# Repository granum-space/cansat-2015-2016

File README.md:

# main
Код для полётного модуля

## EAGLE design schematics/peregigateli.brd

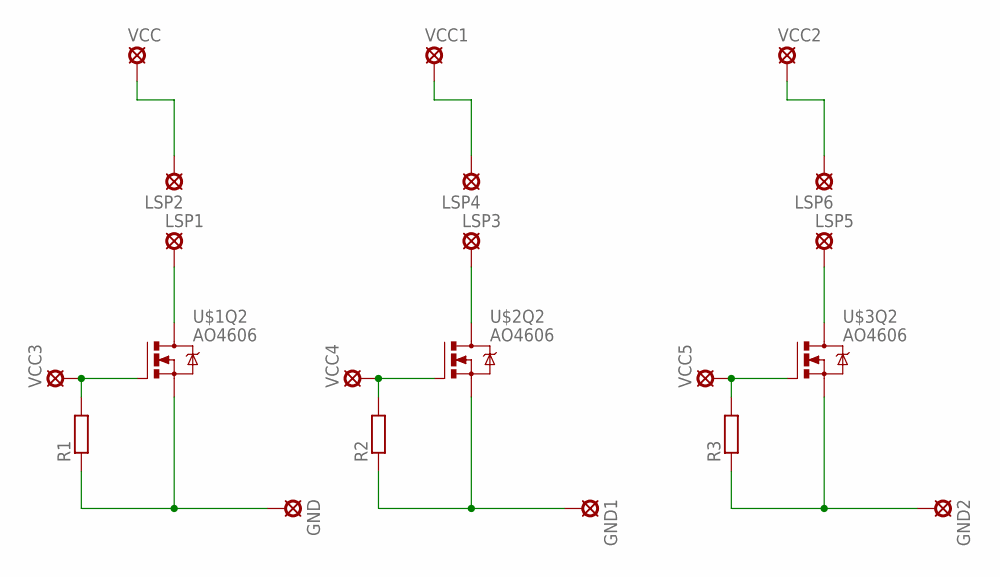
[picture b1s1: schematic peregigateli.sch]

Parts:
GND, GND1, GND2: LSP10
LSP1, LSP2, LSP3, LSP4, LSP5, LSP6: LSP10
R1, R2, R3: R-EU_0207/10; 0207/10
U$1, U$2, U$3: AO4606; SOIC-8
VCC, VCC1, VCC2, VCC3, VCC4, VCC5: LSP10

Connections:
unnamed: LSP1.MP, U$1.7 (D), U$1.8 (D)
unnamed: R1.2, U$1.2 (G), VCC3.MP
unnamed: GND.MP, R1.1, U$1.1 (S)
unnamed: LSP3.MP, U$2.7 (D), U$2.8 (D)
unnamed: LSP4.MP, VCC1.MP
unnamed: GND1.MP, R2.1, U$2.1 (S)
unnamed: LSP5.MP, U$3.7 (D), U$3.8 (D)
unnamed: LSP6.MP, VCC2.MP
unnamed: GND2.MP, R3.1, U$3.1 (S)
unnamed: LSP2.MP, VCC.MP
unnamed: R2.2, U$2.2 (G), VCC4.MP
unnamed: R3.2, U$3.2 (G), VCC5.MP

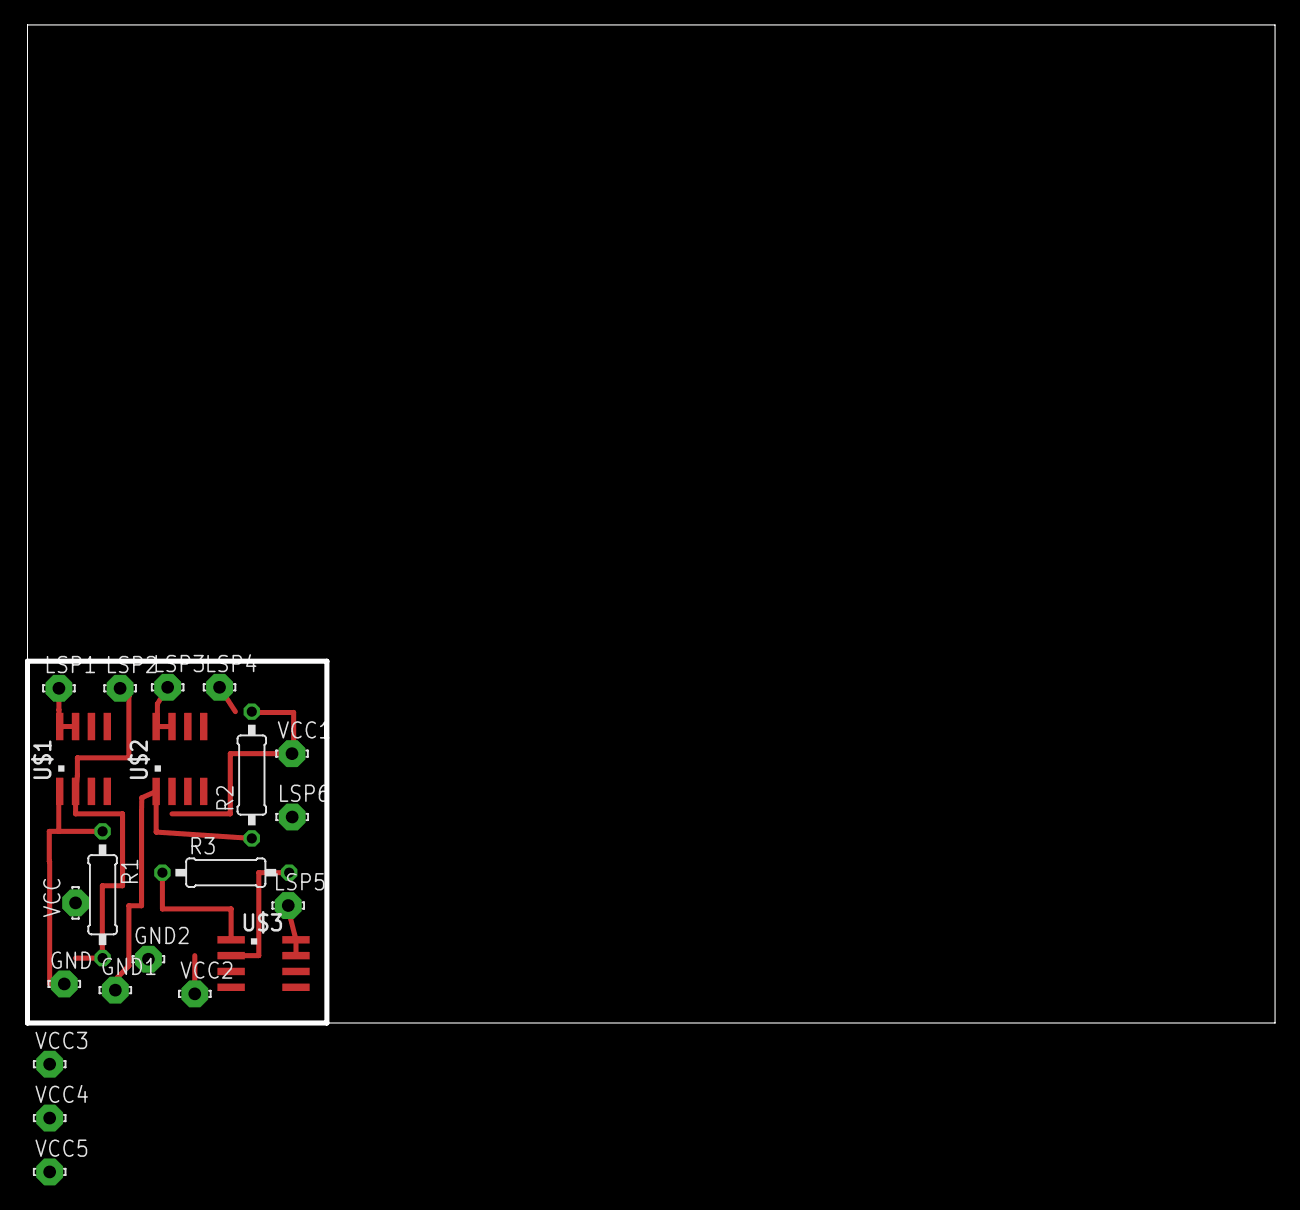
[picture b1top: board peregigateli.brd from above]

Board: 2 copper layers, 100.0 x 80.0 mm, 21 parts (0 on the bottom side), 12 nets.

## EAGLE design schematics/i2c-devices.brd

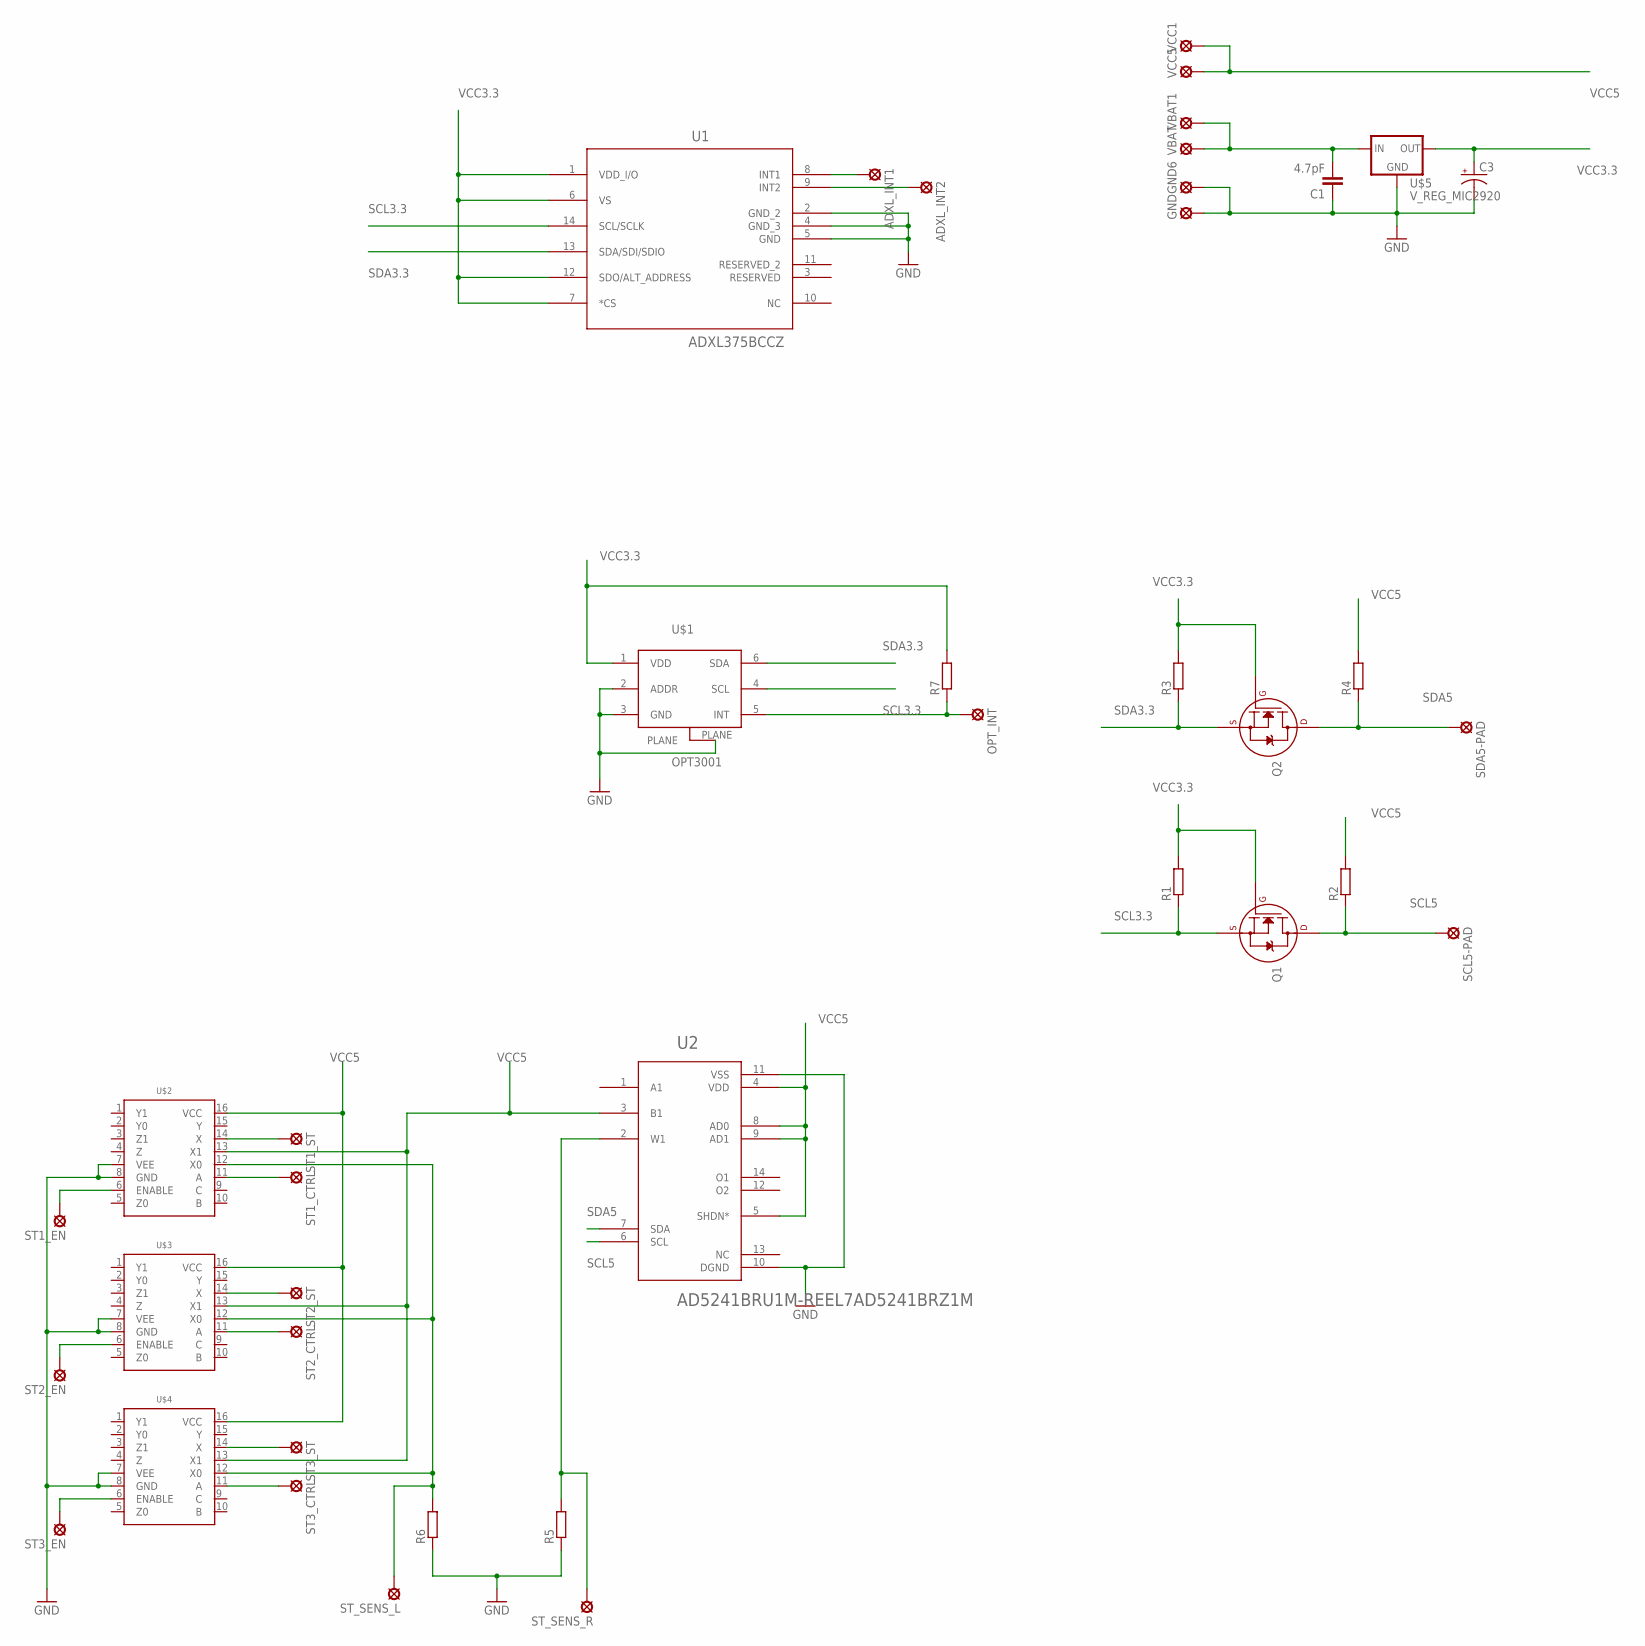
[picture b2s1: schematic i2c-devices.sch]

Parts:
ADXL_INT1, ADXL_INT2: LSP10
C1: 4.7pF; C0603
C3: CAP_POL3528; EIA3528
GND, GND6: LSP10
OPT_INT: LSP10
Q1, Q2: 2N7002_SOT23; SOT-23
R1, R2, R3, R4, R5, R6, R7: R-EU_R0805; R0805
SCL5-PAD: LSP10
SDA5-PAD: LSP10
ST1_CTRL, ST1_EN, ST1_ST, ST2_CTRL, ST2_EN, ST2_ST, ST3_CTRL, ST3_EN, ST3_ST: LSP10
ST_SENS_L: LSP10
ST_SENS_R: LSP10
U1: ADXL375BCCZ; LGA_CC-14-1
U2: AD5241BRU1M-REEL7AD5241BRZ1M; SOIC-14
U$1: OPT3001
U$2, U$3, U$4: MC74HC4051AMC74HC4051AG; SOIC-16
U$5: V_REG_MIC2920; SOT223
VBAT, VBAT1: LSP10
VCC1, VCC5: LSP10

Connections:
GND: C1.1, C3.C (-), GND.MP, GND6.MP, R5.1, R6.1, U1.2 (GND_2), U1.4 (GND_3), U1.5 (GND), U2.10 (DGND), U2.11 (VSS), U$1.2 (ADDR), U$1.3 (GND), U$1.PLANE, U$2.7 (VEE), U$2.8 (GND), U$3.7 (VEE), U$3.8 (GND), U$4.7 (VEE), U$4.8 (GND), U$5.2 (GND)
unnamed: C1.2, U$5.1 (IN), VBAT.MP, VBAT1.MP
unnamed: ST1_ST.MP, U$2.14 (X)
unnamed: ST1_EN.MP, U$2.6 (ENABLE)
unnamed: ST3_EN.MP, U$4.6 (ENABLE)
unnamed: ST2_ST.MP, U$3.14 (X)
unnamed: ST3_ST.MP, U$4.14 (X)
unnamed: R5.2, ST_SENS_R.MP, U2.2 (W1)
unnamed: R6.2, ST_SENS_L.MP, U$2.12 (X0), U$3.12 (X0), U$4.12 (X0)
unnamed: ST2_EN.MP, U$3.6 (ENABLE)
unnamed: ST2_CTRL.MP, U$3.11 (A)
unnamed: ST3_CTRL.MP, U$4.11 (A)
unnamed: ST1_CTRL.MP, U$2.11 (A)
unnamed: OPT_INT.MP, R7.1, U$1.5 (INT)
unnamed: ADXL_INT1.MP, U1.8 (INT1)
unnamed: ADXL_INT2.MP, U1.9 (INT2)
SCL3.3: Q1.2 (S), R1.1, U1.14 (SCL/SCLK), U$1.4 (SCL)
SCL5: Q1.3 (D), R2.1, SCL5-PAD.MP, U2.6 (SCL)
SDA3.3: Q2.2 (S), R3.1, U1.13 (SDA/SDI/SDIO), U$1.6 (SDA)
SDA5: Q2.3 (D), R4.1, SDA5-PAD.MP, U2.7 (SDA)
VCC3.3: C3.A (+), Q1.1 (G), Q2.1 (G), R1.2, R3.2, R7.2, U1.1 (VDD_I/O), U1.6 (VS), U1.7 (*CS), U1.12 (SDO/ALT_ADDRESS), U$1.1 (VDD), U$5.3 (OUT)
VCC5: R2.2, R4.2, U2.3 (B1), U2.4 (VDD), U2.5 (SHDN*), U2.8 (AD0), U2.9 (AD1), U$2.13 (X1), U$2.16 (VCC), U$3.13 (X1), U$3.16 (VCC), U$4.13 (X1), U$4.16 (VCC), VCC1.MP, VCC5.MP

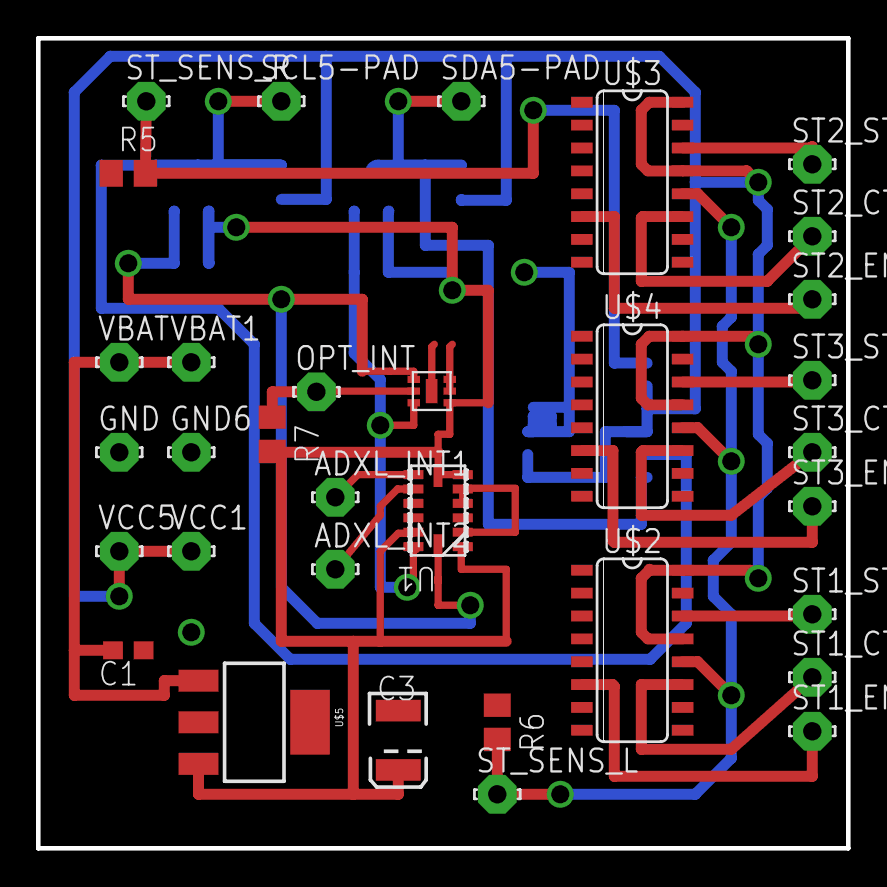
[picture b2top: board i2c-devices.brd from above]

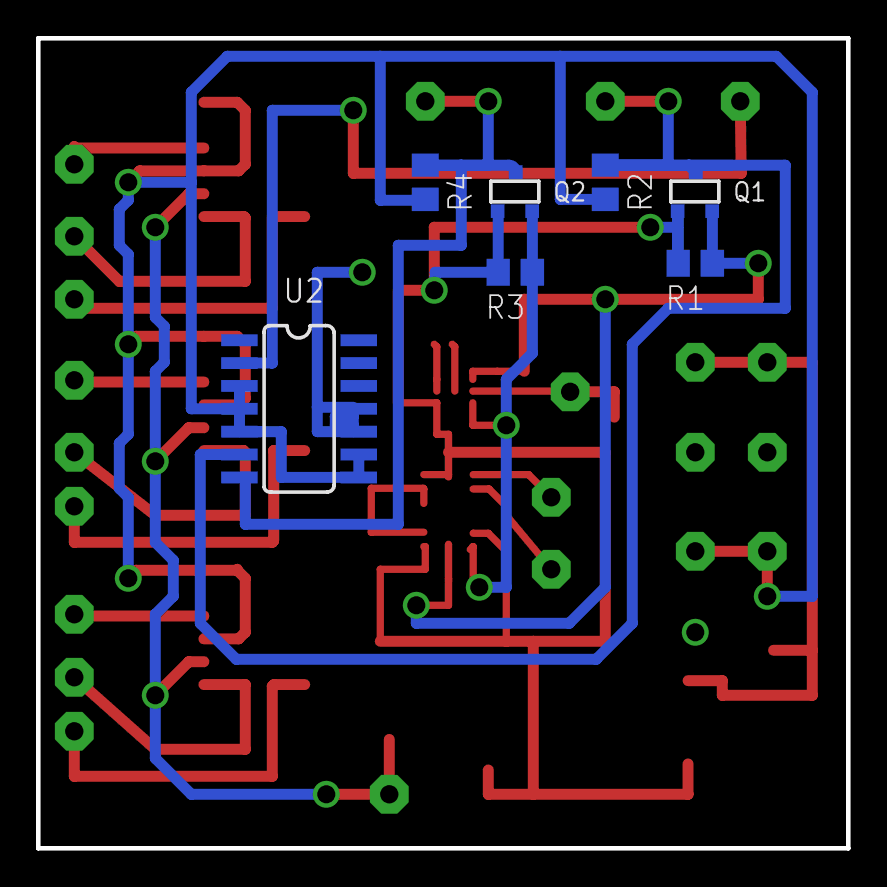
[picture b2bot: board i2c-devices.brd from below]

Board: 2 copper layers, 45.0 x 45.0 mm, 40 parts (7 on the bottom side), 22 nets.

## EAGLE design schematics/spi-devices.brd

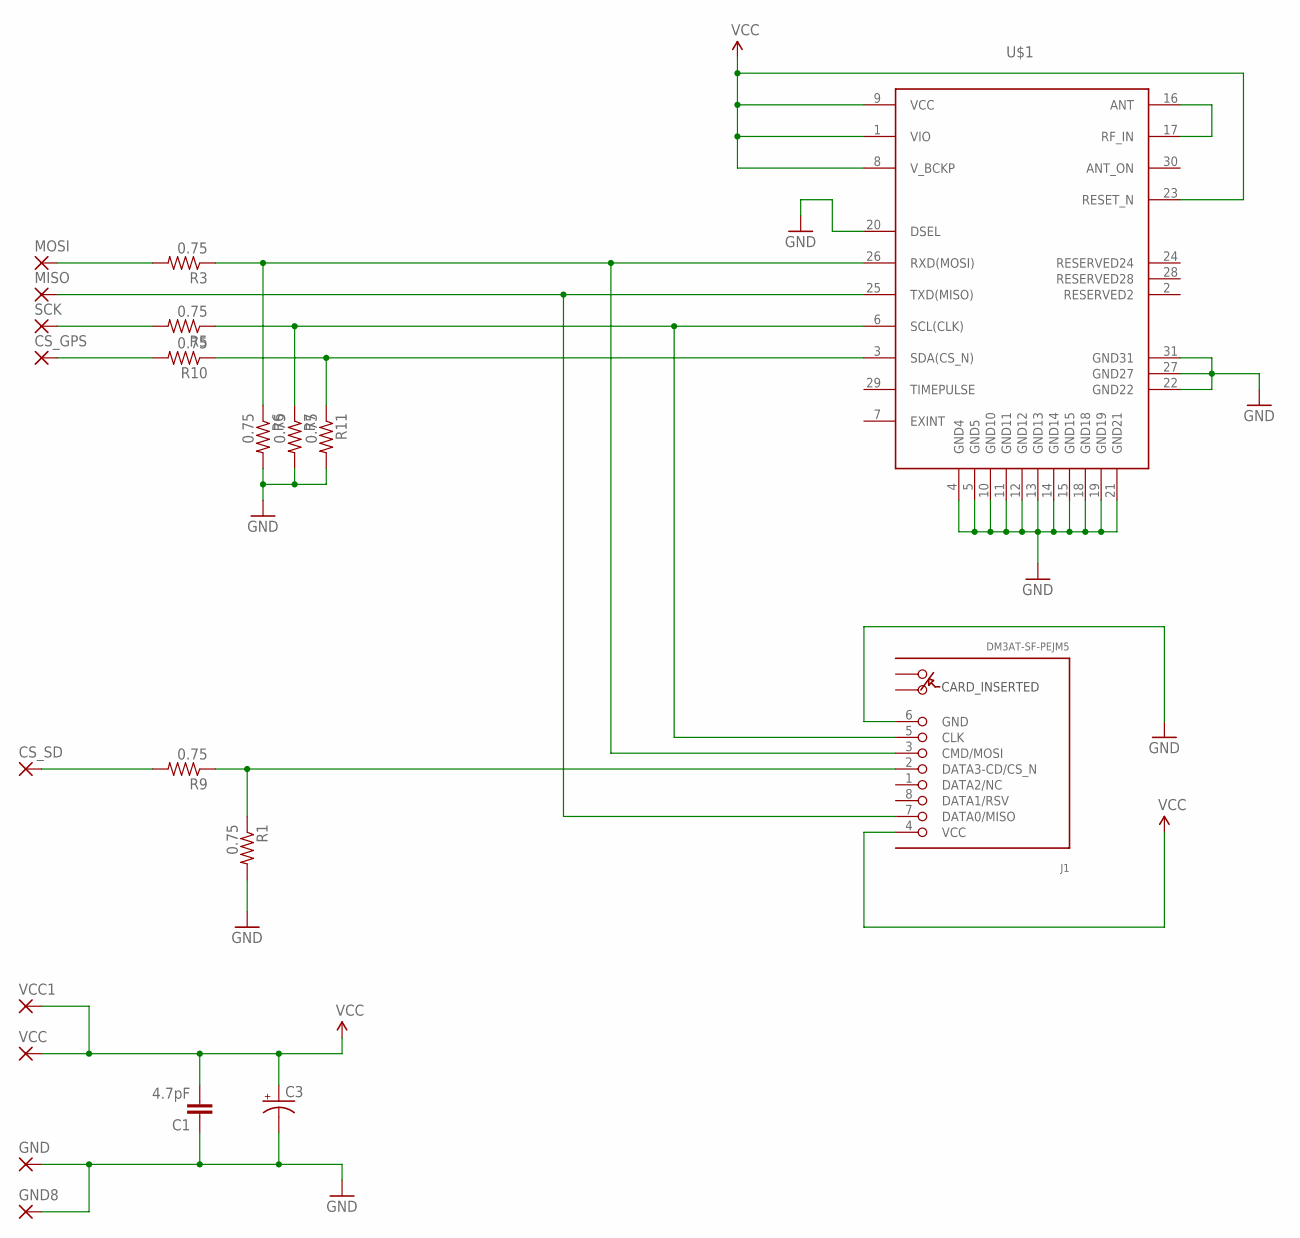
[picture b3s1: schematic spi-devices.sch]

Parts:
C1: 4.7pF; C0603
C3: CAP_POL3528; EIA3528
CS_GPS: 2,54/0,9
CS_SD: 2,54/0,9
GND, GND8: 2,54/0,9
J1: DM3AT-SF-PEJM5
MISO: 2,54/0,9
MOSI: 2,54/0,9
R1, R3, R5, R6, R7, R9, R10, R11: 0.75; 0805
SCK: 2,54/0,9
U$1: CAM-M8Q
VCC, VCC1: 2,54/0,9

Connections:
CS_GPS: CS_GPS.1, R10.2
CS_GPS_3.3: R10.1, R11.1, U$1.3 (SDA(CS_N))
CS_SD: CS_SD.1, R9.2
CS_SD_3.3: J1.2 (DATA3-CD/CS_N), R1.1, R9.1
GND: C1.1, C3.C (-), GND.1, GND8.1, J1.6 (GND), R1.2, R6.2, R7.2, R11.2, U$1.4 (GND4), U$1.5 (GND5), U$1.10 (GND10), U$1.11 (GND11), U$1.12 (GND12), U$1.13 (GND13), U$1.14 (GND14), U$1.15 (GND15), U$1.18 (GND18), U$1.19 (GND19), U$1.20 (DSEL), U$1.21 (GND21), U$1.22 (GND22), U$1.27 (GND27), U$1.31 (GND31)
MISO: J1.7 (DATA0/MISO), MISO.1, U$1.25 (TXD(MISO))
MOSI: MOSI.1, R3.2
MOSI3.3: J1.3 (CMD/MOSI), R3.1, R6.1, U$1.26 (RXD(MOSI))
RF: U$1.16 (ANT), U$1.17 (RF_IN)
SCK: R5.2, SCK.1
SCK3.3: J1.5 (CLK), R5.1, R7.1, U$1.6 (SCL(CLK))
VCC: C1.2, C3.A (+), J1.4 (VCC), U$1.1 (VIO), U$1.8 (V_BCKP), U$1.9 (VCC), U$1.23 (RESET_N), VCC.1, VCC1.1

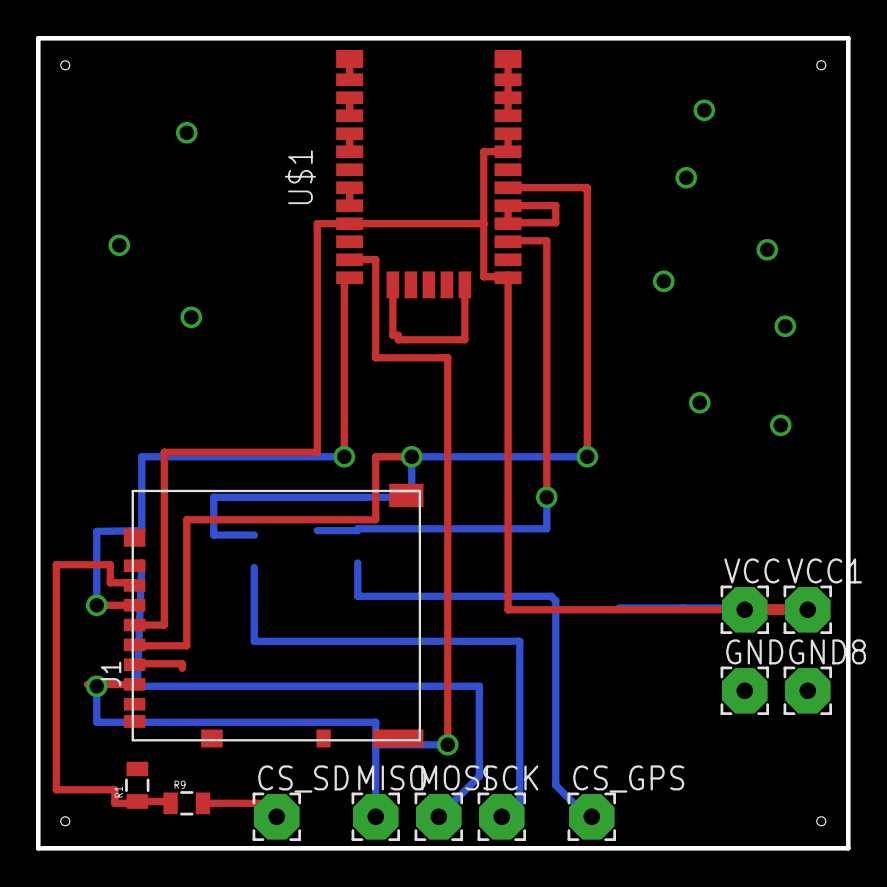
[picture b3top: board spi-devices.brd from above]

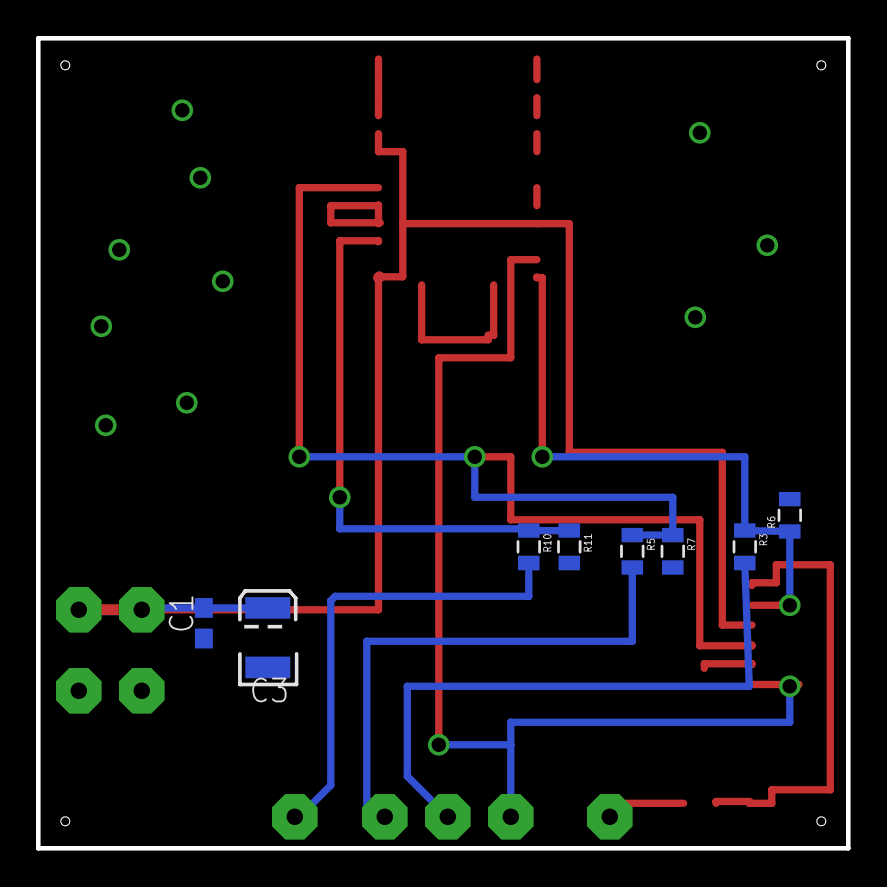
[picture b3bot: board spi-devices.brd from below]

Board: 2 copper layers, 45.0 x 45.0 mm, 21 parts (8 on the bottom side), 12 nets.

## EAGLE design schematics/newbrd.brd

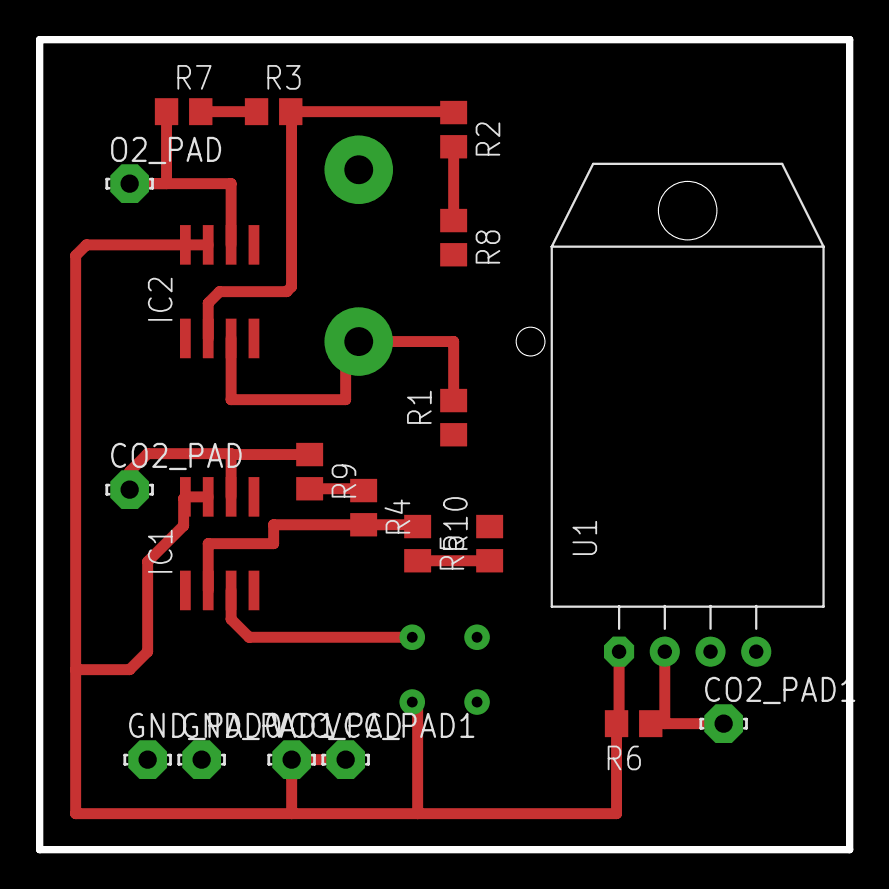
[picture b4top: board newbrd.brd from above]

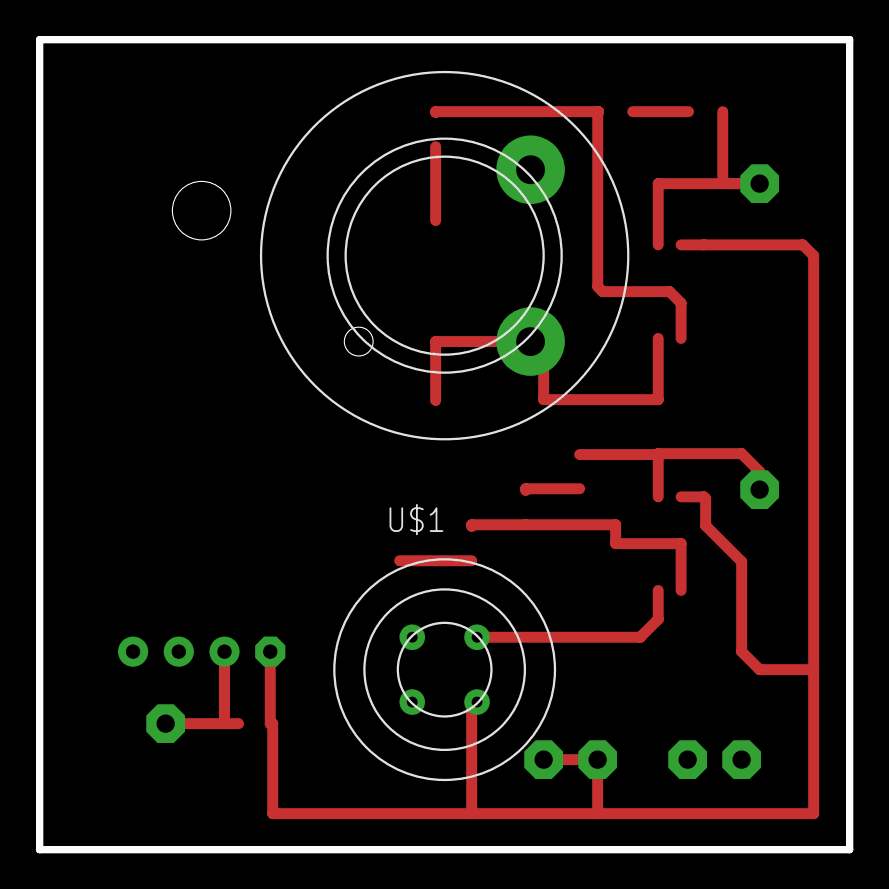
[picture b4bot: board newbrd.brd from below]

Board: 2 copper layers, 45.0 x 45.0 mm, 22 parts (2 on the bottom side), 13 nets.

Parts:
CO2_PAD, CO2_PAD1: LSP10
GND_PAD0, GND_PAD1: LSP10
IC1, IC2: TLC271D; SO08
O2_PAD: LSP10
R1, R2, R3, R4, R5, R6, R7, R8, R9, R10: R0805
U1: RHT03_DHT-22/RA
U$1: TGS4161
U$2: O2-A2
VCC_PAD, VCC_PAD1: LSP10

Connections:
GND: GND_PAD0.MP, GND_PAD1.MP, IC1.4, IC2.4, R1.1, R8.2, R10.2, U1.GND, U$1.3, U$1.4, U$2.GND
unnamed: IC2.3, R1.2, U$2.VOUT
unnamed: CO2_PAD1.MP, R6.1, U1.DATA
unnamed: IC2.2, R2.1, R3.2
unnamed: IC2.6, O2_PAD.MP, R7.1
unnamed: IC1.3, U$1.2
unnamed: CO2_PAD.MP, IC1.6, R9.1
unnamed: R3.1, R7.2
unnamed: R2.2, R8.1
unnamed: R4.1, R9.2
unnamed: R5.2, R10.1
unnamed: IC1.2, R4.2, R5.1
VCC: IC1.7, IC1.8, IC2.7, IC2.8, R6.2, U1.VDD, U$1.1, VCC_PAD.MP, VCC_PAD1.MP

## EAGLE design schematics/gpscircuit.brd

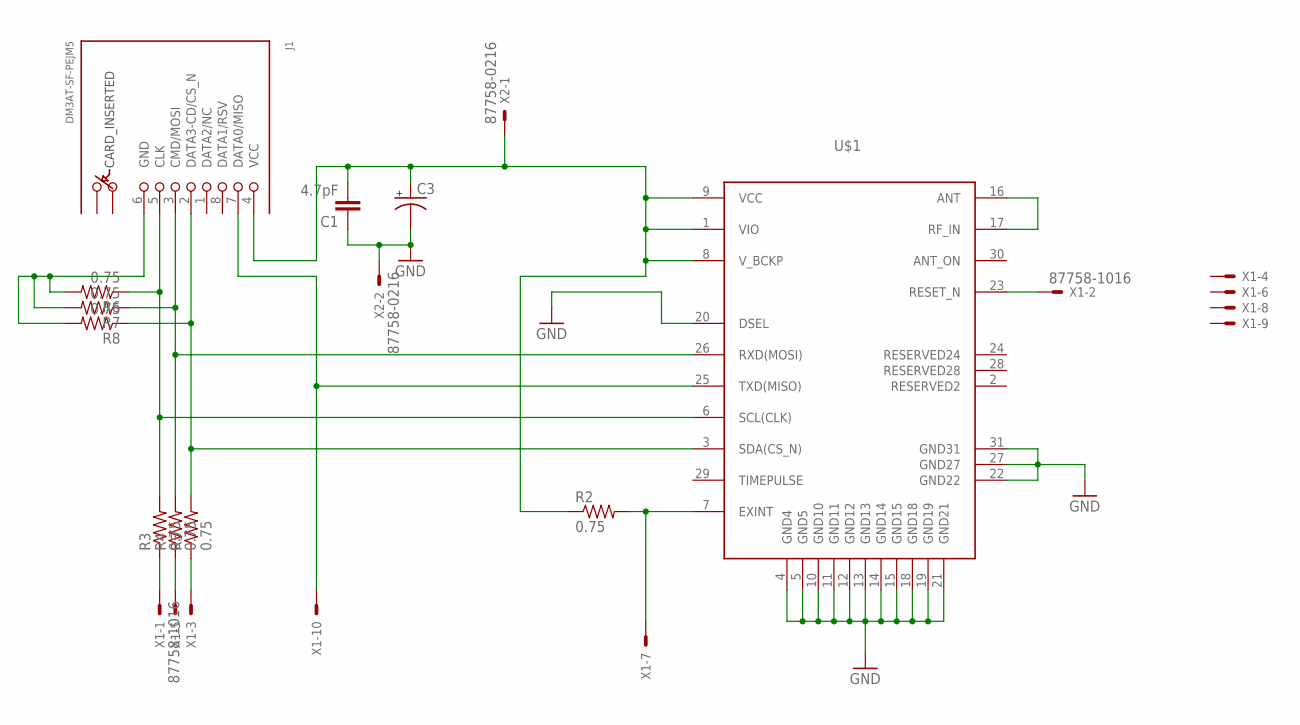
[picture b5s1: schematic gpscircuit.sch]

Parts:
C1: 4.7pF; C0603
C3: CAP_POL3528; EIA3528
J1: DM3AT-SF-PEJM5
R2, R3, R4, R5, R6, R7, R8: 0.75; 0805
U$1: CAM-M8Q
X1: 87758-1016
X2: 87758-0216

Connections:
3.3V: C1.2, C3.A (+), J1.4 (VCC), R2.1, U$1.1 (VIO), U$1.8 (V_BCKP), U$1.9 (VCC), X2.1
GND: C1.1, C3.C (-), U$1.4 (GND4), U$1.5 (GND5), U$1.10 (GND10), U$1.11 (GND11), U$1.12 (GND12), U$1.13 (GND13), U$1.14 (GND14), U$1.15 (GND15), U$1.18 (GND18), U$1.19 (GND19), U$1.20 (DSEL), U$1.21 (GND21), U$1.22 (GND22), U$1.27 (GND27), U$1.31 (GND31), X2.2
unnamed: U$1.16 (ANT), U$1.17 (RF_IN)
unnamed: U$1.23 (RESET_N), X1.2
unnamed: R2.2, U$1.7 (EXINT), X1.7
unnamed: J1.7 (DATA0/MISO), U$1.25 (TXD(MISO)), X1.10
unnamed: R4.1, X1.5
unnamed: R5.1, X1.3
unnamed: J1.6 (GND), R6.2, R7.2, R8.2
unnamed: R3.1, X1.1
unnamed: J1.5 (CLK), R3.2, R6.1, U$1.6 (SCL(CLK))
unnamed: J1.2 (DATA3-CD/CS_N), R5.2, R8.1, U$1.3 (SDA(CS_N))
unnamed: J1.3 (CMD/MOSI), R4.2, R7.1, U$1.26 (RXD(MOSI))

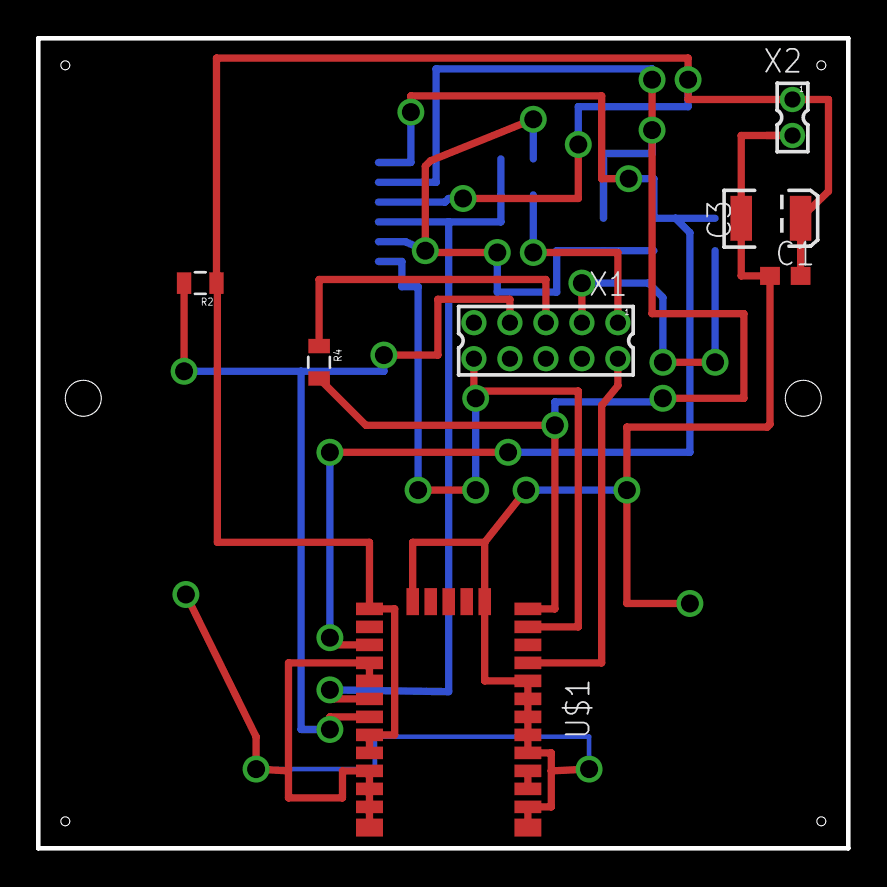
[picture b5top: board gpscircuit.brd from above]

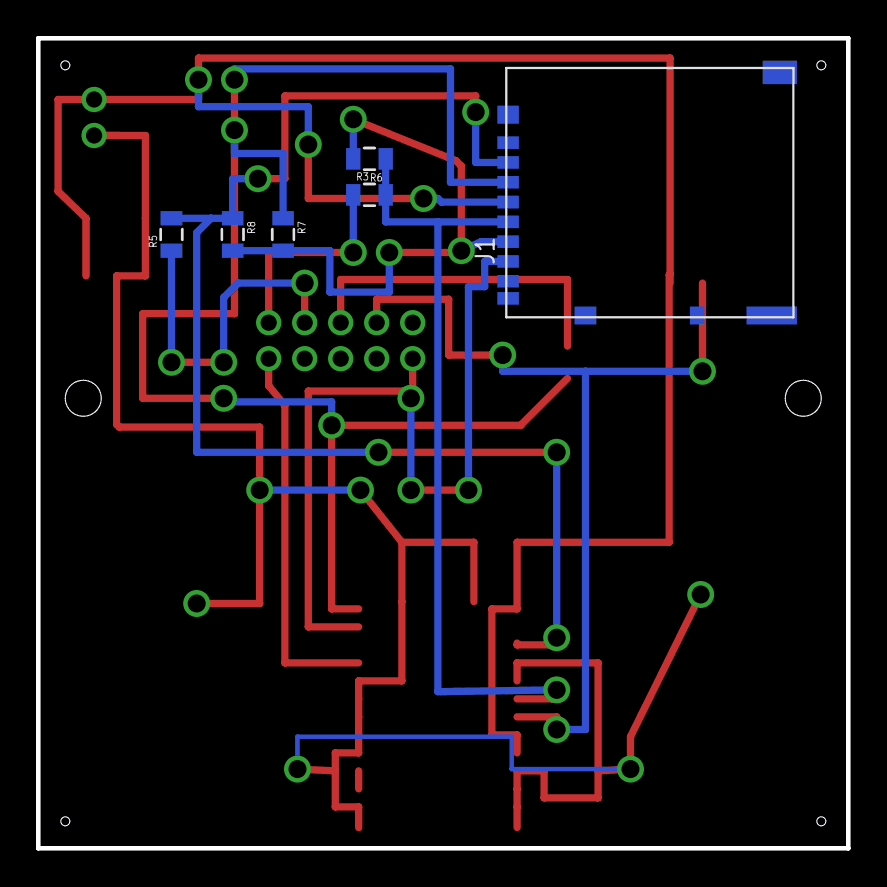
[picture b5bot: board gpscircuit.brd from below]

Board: 2 copper layers, 45.0 x 45.0 mm, 13 parts (6 on the bottom side), 13 nets.

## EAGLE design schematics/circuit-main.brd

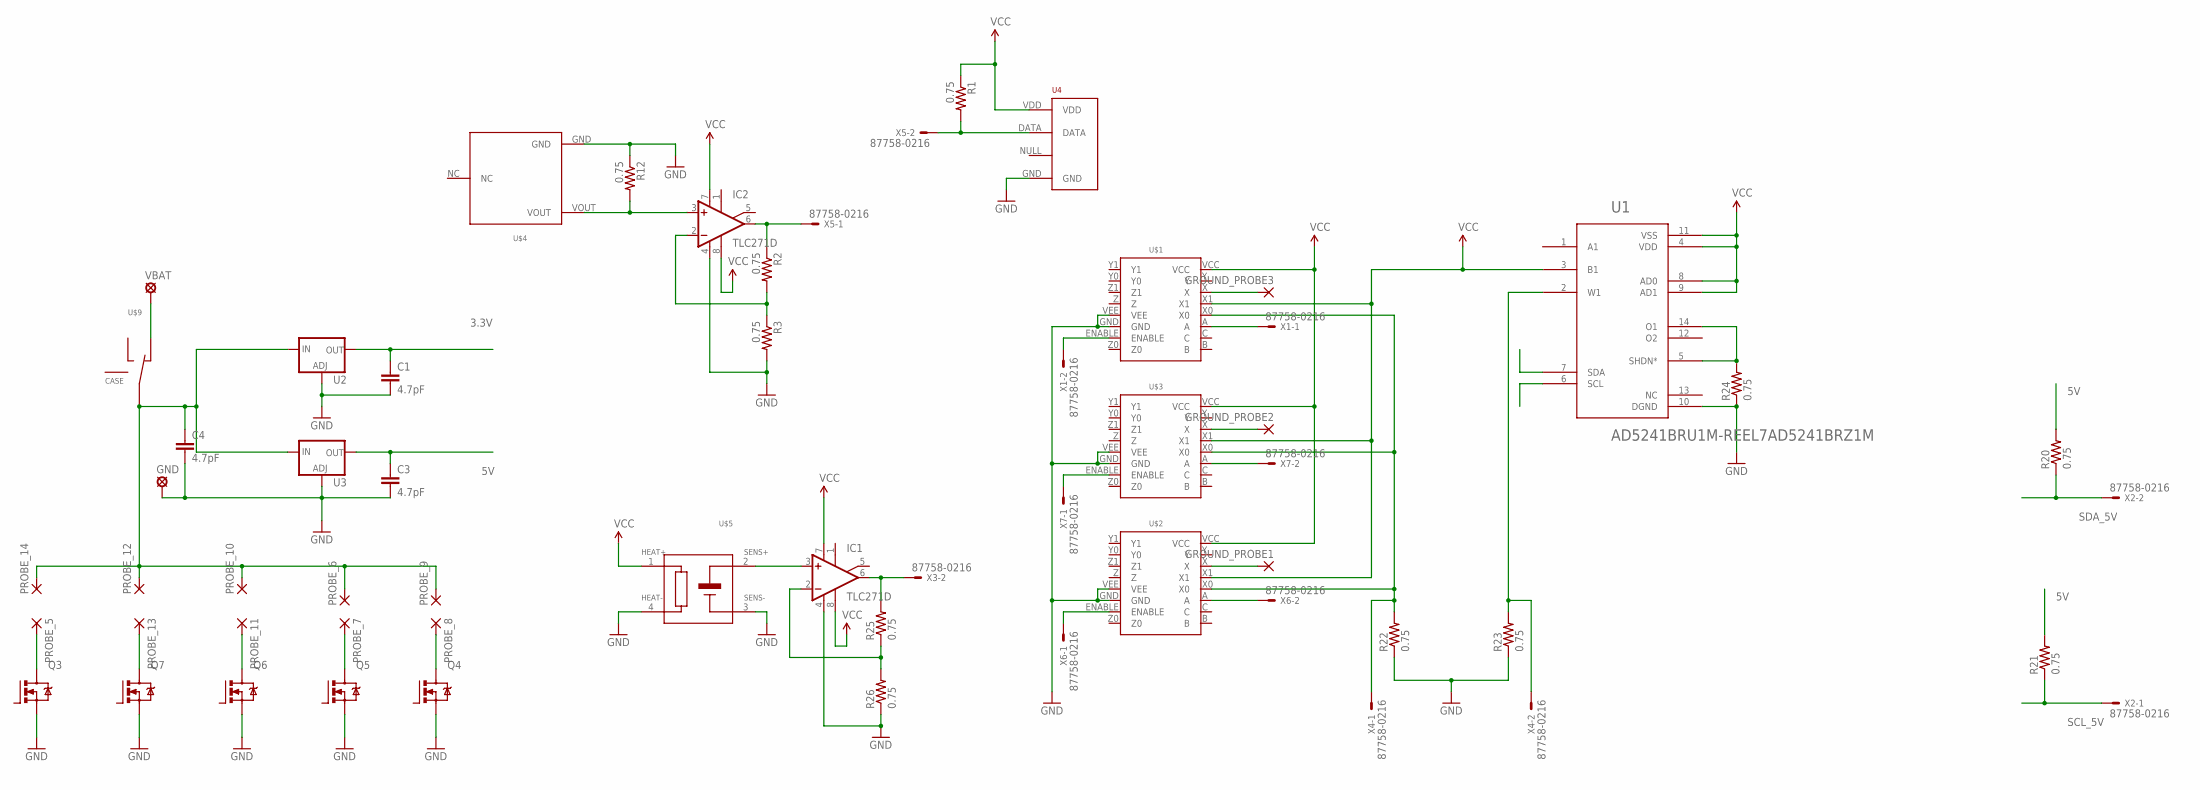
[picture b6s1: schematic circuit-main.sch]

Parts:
C1, C3, C4: 4.7pF; 0603-CAP
GND: LSP10
GROUND_PROBE1, GROUND_PROBE2, GROUND_PROBE3: 2,54/0,8
IC1, IC2: TLC271D; SO08
PROBE_5, PROBE_6, PROBE_7, PROBE_8, PROBE_9, PROBE_10, PROBE_11, PROBE_12, PROBE_13, PROBE_14: 2,54/0,8
Q3, Q4, Q5, Q6, Q7: NTR4501N; SOT-23
R1, R2, R3, R12, R20, R21, R22, R23, R24, R25, R26: 0.75; 0805
U1: AD5241BRU1M-REEL7AD5241BRZ1M; SOIC-14
U2: TLV1117-33; SOT223
U3: LD1117S50; SOT223
U4: RHT03_DHT-22_AM2302RA; RHT03_DHT-22/RA
U$1, U$2, U$3: MC74HC4051A; SOIC16
U$4: O2-A2
U$5: TGS4161
U$9: SS-8
VBAT: LSP10
X1, X2, X3, X4, X5, X6, X7: 87758-0216

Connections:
3.3V: C1.1, R1.1, U2.2 (OUT), U2.4 (OUT), U4.VDD
5V: C3.1, IC1.7 (V+), IC1.8 (OPT), IC2.7 (V+), IC2.8 (OPT), R20.2, R21.2, U1.3 (B1), U1.4 (VDD), U1.8 (AD0), U1.9 (AD1), U1.11 (VSS), U3.2 (OUT), U3.4 (OUT), U$1.VCC, U$1.X1, U$2.VCC, U$2.X1, U$3.VCC, U$3.X1, U$5.1 (HEAT+)
GND: C1.2, C3.2, C4.2, GND.MP, IC1.4 (V-), IC2.4 (V-), Q3.2 (S), Q4.2 (S), Q5.2 (S), Q6.2 (S), Q7.2 (S), R3.2, R12.1, R22.1, R23.1, R24.1, R26.1, U1.10 (DGND), U2.1 (ADJ), U3.1 (ADJ), U4.GND, U$1.GND, U$1.VEE, U$2.GND, U$2.VEE, U$3.GND, U$3.VEE, U$4.GND, U$5.3 (SENS-), U$5.4 (HEAT-)
unnamed: IC2.6 (OUT), R2.1, X5.1
unnamed: GROUND_PROBE3.1, U$1.X
unnamed: R1.2, U4.DATA, X5.2
unnamed: IC2.2 (-IN), R2.2, R3.1
unnamed: GROUND_PROBE2.1, U$3.X
unnamed: GROUND_PROBE1.1, U$2.X
unnamed: R23.2, U1.2 (W1), X4.2
unnamed: R22.2, U$1.X0, U$2.X0, U$3.X0, X4.1
unnamed: U$3.ENABLE, X7.1
unnamed: U$3.A, X7.2
unnamed: U$2.A, X6.2
unnamed: U$1.A, X1.1
unnamed: U$1.ENABLE, X1.2
unnamed: U$2.ENABLE, X6.1
unnamed: PROBE_5.1, Q3.3 (D)
unnamed: R24.2, U1.5 (SHDN*), U1.14 (O1)
unnamed: IC1.3 (+IN), U$5.2 (SENS+)
unnamed: PROBE_8.1, Q4.3 (D)
unnamed: IC1.6 (OUT), R25.2, X3.2
unnamed: PROBE_7.1, Q5.3 (D)
unnamed: PROBE_11.1, Q6.3 (D)
unnamed: PROBE_13.1, Q7.3 (D)
unnamed: U$9.P2, VBAT.MP
unnamed: IC2.3 (+IN), R12.2, U$4.VOUT
unnamed: IC1.2 (-IN), R25.1, R26.2
SCL_5V: R21.1, U1.6 (SCL), X2.1
SDA_5V: R20.1, U1.7 (SDA), X2.2
VBAT: C4.1, PROBE_6.1, PROBE_9.1, PROBE_10.1, PROBE_12.1, PROBE_14.1, U2.3 (IN), U3.3 (IN), U$9.COM

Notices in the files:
parts and their libraries:
SparkFun-Capacitors: Licensing: Creative Commons ShareAlike 4.0 International - https://creativecommons.org/licenses/by-sa/4.0
